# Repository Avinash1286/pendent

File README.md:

# AURA / pendent

**Capture the context of your life.**

[Explore the A03 showcase](https://pendent-eight.vercel.app) · [Watch the A03 film](https://pendent-eight.vercel.app/film/aura-launch.mp4) · [Download the A03 release](https://github.com/Avinash1286/pendent/releases/tag/a03-context-dev) · [Run the notes portal](portal/README.md)

An open product-development project for a compact necklace AI note-taking device. Electronics, printable industrial design, chip firmware, local transcription, a Next.js / Convex notes portal, an interactive Three.js showcase and a Hyperframes launch film live together here.

## A04 circular redesign — in progress

A04 is a fresh circular design created through **KiCad MCP**, with a physical microphone disconnect, separate update-storage hardware and a source-preserving audio protocol. The current M2 mechanism is **43 mm across and 12.2 mm deep**, accommodating the actual 1.6 mm draft PCB and a 4.3 mm pack allowance. An 11.2 mm variant requires an unselected thinner pack. The earlier 40 × 10 mm goal remains an aspiration, not the dimensions of these files. **A04 is not ready to fabricate, print as a complete device, wear or sell.**

[Full objective and evidence gates](docs/a04/requirements.md) · [New KiCad project](hardware/a04/aura-a04.kicad_pro) · [Mechanical contract](docs/a04/industrial-design.md) · [Software contract and recovery tests](docs/a04/software-contract.md) · [Omi source review](docs/research/omi-review.md)

The current checkpoint includes a **72-reference schematic candidate**, monitored microphone driver, bounded audio FIFO, recorder, shared C/Python Opus archive, recoverable NAND journal and SPI command core. The [storage owner and release outbox](firmware/a04/STORAGE.md) now reserve capture identities and release explicitly authorized recordings through a durable grant, with real C/Python audio round trips on modeled NAND. The nRF52840 DK build records linked memory and symbols in [the current wired-bench ELF resource report](firmware/a04/bench/verification/arm-resources.json). Host checks cover driver faults, privacy/stop ordering, capture boundaries, interrupted writes and preserved audio during storage reuse. The companion passes 131 tests; the earlier portal checkpoint retains 24. The schematic still has one ERC error, nine warnings and three net-name mismatches; the board is not placed or routed. [Native capture evidence](docs/a04/native-capture-verification.json) · [Firmware and audio evidence](firmware/a04/README.md) · [Route to your first physical wearable](docs/research/aura-first-wearable.md).

The working local software path now takes a **real C-generated audio archive through local Whisper transcription into Next.js/Convex**. It preserves the original capture, exact audio duration, bookmarks and transcript provenance. Interrupted captures remain explicit, and token rotation does not duplicate an existing source. These checks use synthetic speech; microphone, Bluetooth and worn-device behavior still need physical validation. [Try the archive importer](companion/README.md#a04-archive-import--040) · [Read the verification](companion/VERIFICATION.md) · [Portal provenance and recovery](docs/a04/portal-provenance.md).

The new [first spoken-note bench](firmware/a04/bench/README.md) provides a separate nRF52840 DK application, reviewed microphone/NAND wiring and a UART capture/export tool. It connects the actual drivers and storage code, with explicit recording permission and verified local publication. The image cross-builds; 31 host-client tests and five C orchestration groups cover its software behavior. **No physical audio has been recorded or board flashed.** This prepares the hardware experiment needed before the custom PCB and wearable can be qualified.

The [native Android companion](mobile/android/README.md) provides a local recording library: select an A04 archive, validate its original bytes and Opus audio, listen back, write context, and explicitly copy/share that context with an AI chat. The new [durable download store](mobile/android/DOWNLOADS.md) commits exact source records and resume metadata together, replays saved prefixes after reopening, and passes completed downloads through the library's actual decoder and publication checks. The current [development APK](https://github.com/Avinash1286/pendent/releases/tag/a04-android-recovery-dev) passed **29 Android emulator cases / 428 assertions**, with zero lint findings. The shared complete/incremental validator and transfer codecs pass **30 JVM groups / 82,213 checks**, including six incremental groups / 49,471 checks and 19 complete C-generated archives. The real Android GATT path also passed **four virtual-link cases / 33 assertions at each of MTU 23 and 517**, including a second connection without duplicate library entries. The peripheral is a Python fixture, not Zephyr firmware or physical radio. Original recordings and physical-OPEN provenance remain preserved. The Activity still exposes file import; Bluetooth download is not yet a user-facing feature. [Verification](mobile/android/VERIFICATION.md).

A [bounded journal cursor](firmware/a04/JOURNAL-CURSOR.md) prepares pendant-to-phone recovery: exact-record resume, at most one NAND read per step, source checks before streaming and again before completion, and cancellation that preserves the original recording. It is exercised through the wired DK export path. A portable [transfer command owner](docs/a04/transfer-wire-v1.md) adds ordered retries, owned capture selection and protection against stale response callbacks; 12 C test groups pass. Android now has the durable source store, library handoff and [foreground recovery owner with a native GATT client](mobile/android/RECOVERY.md). The device radio DK adapter is now implemented separately; owner enrollment, matching Android proof integration and consumer UI remain, followed by physical recovery and OS background qualification. [Transport integration plan](docs/a04/mobile-transport.md).

The new [authenticated Bluetooth DK application](firmware/a04/radio/README.md) integrates the actual transfer engine with the recording/storage owner. It adds a physically bounded pairing window, authenticated LE Secure Connections and fresh owner proof before archive access. Eighteen GATT/transfer groups, twelve C authentication groups and nine pairing-policy groups pass with their documented modeled boundaries. The ARM image uses 243,652 bytes RAM, leaving 18,492 bytes unallocated; runtime headroom is unmeasured. [Download the DK development build](https://github.com/Avinash1286/pendent/releases/tag/a04-radio-dk-dev). Consumer enrollment, the matching Android proof exchange and physical radio/capture trials remain; the older Android/Bumble tests do not execute this firmware.

The **M2 S1 mechanism** keeps the removable bezel and supported PCB, replacing inadequate resin bending links with a separate steel shoe/support and insulating contact pad. Each depth variant contains **12 polymer part models, three hardware form models and two unpowered gauges**. The metal/film forms are not functional resin-print instructions. Mesh and sampled motion checks cover the revised assembly; analytical force screening supports further unpowered joint testing. Materials, tolerances, switch endpoints, all 72 native PCB features, the battery and real assembly remain unqualified. [Blender source, parts and checks](enclosure/a04/mechanism-m2/README.md) · [Steel development drawings and 1:1 DXF profiles](enclosure/a04/mechanism-m2-manufacturing/README.md) · [Earlier process coupon kit](enclosure/a04/coupon/README.md).

<details>
<summary>Inspect the A04 M2 experimental parts</summary>

The exploded offsets show individual parts; separate motion reports check sampled assembly paths. Read the [remaining assembly and release gates](enclosure/a04/mechanism-m2/README.md#assembly-and-release-gates) before using these files. The [M1 experiment and its failures](enclosure/a04/mechanism/README.md) and [original 40 mm appearance study](enclosure/a04/study/aura-a04-study.png) remain available as earlier work.

</details>

The website, film, PCB and eight-part print kit linked below belong to the earlier **A03 development release**. They are retained for reproducibility and are not A04 deliverables.

## A03 development release

## Launch film

**[▶ Watch the 44-second film](https://pendent-eight.vercel.app/film/aura-launch.mp4)** · [Download the 1080p MP4](https://github.com/Avinash1286/pendent/releases/download/a03-context-dev/aura-launch.mp4) · [Hyperframes source](film/aura-launch/README.md)

See the pendant from the outside in, including its interior and assembly animation. Click the poster to play.

## 3D-printable parts

Rendered from the actual STL files; individual views are not to scale. The kit includes six device parts and two fit/alignment tools. STL units are millimetres; print orientation and material guidance are in the assembly guide.

[Download all eight STL files](enclosure/aura-a03-print-kit.zip) · [Print and assembly guide](enclosure/PRINTING.md) · [Editable Blender scene](enclosure/aura-product.blend)

## PCB

The **24 × 42 × 0.8 mm, four-layer board**, shown directly from its native KiCad copper layers with illustrative colours. These are prototype files; the 78 courtyard findings still require assembly review.

[Editable KiCad project](hardware/native/aura-a03.kicad_pro) · [Prototype fabrication ZIP](hardware/output/aura-a03-prototype-fabrication.zip) · [Schematic and review files](hardware/native/review/)

## Project status

**A03 context and assembly edition.** [Prototype fabrication files](hardware/native/README.md) are exported from the paired KiCad project: zero unconnected items, schematic mismatches, ERC findings or bare-board DRC errors. **78 unsuppressed courtyard overlaps remain for assembly review.** The case has printable meshes with geometric audits; real fit, battery, acoustic and RF tests remain. Firmware is compiled for the nRF52840 but has not run on an assembled AURA. The notes portal uses real local Convex; cloud setup awaits account terms acceptance. This is not a manufactured or certified device, and no orders or payments are accepted. See the [current release guide](docs/release-a03-context.md) for downloads and verification.

## Project map

New: [Omi codebase review and AURA first-wear plan](docs/research/omi-review.md), with a source-based comparison, all 78 assembly collisions classified, and companion recovery improvements. This review identifies a real component-tolerance conflict that requires an A04 placement revision; it does not qualify A03 for assembled-unit ordering.

| Directory | Contents |
| --- | --- |
| `hardware/` | tscircuit source, routed native KiCad board, readable schematic, BOM and validation evidence |
| `enclosure/` | Blender source, editable generator, printable enclosure meshes, GLB and product renders |
| `firmware/` | Zephyr nRF52840 firmware, reproducible tool setup, flashable build artifacts and native tests |
| `companion/` | Bluetooth sync, CRC verification, local Whisper transcription and optional portal upload |
| `mobile/android/` | Native Kotlin local import, durable download storage and replay, verified playback, private context and explicit sharing; A04 wireless integration pending |
| `portal/` | Next.js / Convex private notes, profiles, Context Pack and read-only MCP endpoint |
| `website/` | Interactive React / Three.js product presentation, deployed directly to Vercel |
| `film/` | Hyperframes composition, original soundtrack and rendered launch video |
| `docs/` | Hardware and product engineering notes |

## Design direction

- 48 × 28 × 10 mm capsule body, 54 mm tall including the bail; 24 × 42 mm PCB.
- A glossy black recording paddle in a satin polymer surround, a bookmark gesture, visible microphone-power indication and a physical privacy slider.
- A physical microphone power disconnect, offline local audio storage and Bluetooth transfer to the companion.
- Dual digital microphones, a protected rechargeable-cell candidate and rear contacts for a magnetic charging dock; the complete dock remains to be designed and qualified.
- Local computer transcription and optional notes upload are implemented. The A04 Android source-import and durable download-storage foundation is available; device-to-phone wireless integration remains future work.
- 16 kHz mono PCM storage has an ideal capacity of about 66 minutes before bad blocks and metadata; battery runtime is unmeasured.

## Start exploring

- [Product and interaction specification](docs/product-design.md)
- [Hardware source and validation](hardware/README.md)
- [Print and assembly guide](enclosure/PRINTING.md) · [eight-part print kit](enclosure/aura-a03-print-kit.zip) · [editable Blender scene](enclosure/aura-product.blend)
- [Firmware build / flash / bring-up](firmware/README.md)
- [Install the local companion](companion/README.md)
- [Run AURA Notes and connect any AI](portal/README.md)
- [Launch film and reproducible Hyperframes source](film/aura-launch/README.md)

The portable **Context Pack** combines your selected notes, source excerpts, personal background and current goals into reviewed Markdown. Copy or attach it in ChatGPT, Claude, Gemini, Grok, or another chat. Compatible MCP clients can instead read explicitly approved live context through a revocable bearer token. Provider buttons do not send data automatically.

## Publication

Sources and generated deliverables are shared here. Website deployment uses Vercel directly; this project does not use GitHub Actions. Dependencies, signing keys, tokens, private local recordings and database files are intentionally excluded. Each workstream documents reproducible setup and the checks actually completed.

## Upstream tools

[tscircuit documentation](https://docs.tscircuit.com/) · [Blender](https://www.blender.org/) · [Three.js](https://threejs.org/docs/) · [Hyperframes](https://github.com/heygen-com/hyperframes) · [Vercel](https://vercel.com/docs)

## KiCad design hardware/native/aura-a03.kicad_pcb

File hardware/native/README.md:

# AURA A03 native prototype project

Open **`aura-a03.kicad_pro` in KiCad 10**. This directory is the paired editable PCB and schematic used for the manufacturing exports. The working routing record remains in `../output/aura-a03-native-routing.kicad_pcb`; the original native schematic reconstruction remains in `../output/aura-a03-electrical.kicad_sch`.

The paired project preserves the verified copper and pads, links every footprint to its actual schematic sheet/symbol UUID, and uses project-relative `AURA_PCB` snapshots. Schematic footprint fields match those snapshots. The 37 intentional NC pads receive their schematic singleton net names while remaining physically isolated; internal numeric net codes may change. `project-linkage.json` records the source and packaged board hashes, unchanged routed geometry and unchanged assignments of all 208 intended connected pins. The source paths follow [KiCad's native netlist identity convention](https://docs.kicad.org/doxygen/common_2netlist__reader_2kicad__netlist__reader_8cpp_source.html).

After editing this paired project, regenerate its exports directly. Rebuilding the tscircuit placement does **not** reproduce the completed native routing and must not overwrite it. Review proposed changes in KiCad's Update PCB from Schematic dialog before applying them; preserve the paired UUIDs and exact snapshot land patterns.

## Manufacturing status

These are connected **prototype fabrication and assembly-review files**. Read `review/manufacturing-checks.json` and `review/drc.json` before submitting them. Native ERC, schematic parity, board connectivity and bare-board DRC each have **zero findings**. The complete DRC report retains **78 `courtyards_overlap` errors** for assembly review. This is not an assembly-approved or qualified consumer-device release.

| Directory / file | Purpose |
| --- | --- |
| `fabrication/gerbers/` | Four copper layers, front/back mask and silkscreen, routed outline and Gerber job metadata |
| `fabrication/drills/` | Separate metric plated/nonplated Excellon files, drill maps and tool report |
| `fabrication/aura-a03.ipc` | IPC-D-356 electrical test netlist |
| `assembly/stencil/` | Separate front/back solder-paste Gerbers; stencil/process review required |
| `assembly/bom.csv` | 57 component candidates with MPNs; the four custom copper-contact features are excluded |
| `assembly/component-centres.csv` | Component body/reference positions and source rotations, corrected for the converter origin offsets |
| `assembly/native-footprint-origins.csv` | Raw KiCad origins for audit; includes custom contacts and must not be substituted blindly for component centres |
| `review/board-layers.pdf` / `review/schematic.pdf` | Readable board layers and six schematic sheets |
| `review/erc.json` / `review/drc.json` | Native, unsuppressed check output |
| `review/native-smd-pad-spacing-audit.json` | 25,158 different-net SMD pad pairs checked against 0.15 mm; zero violations |
| `review/native-via-aperture-audit.json` | 177 vias and 88,500 comparisons against actual SMD copper/paste; zero intersections |
| `review/manufacturing-checks.json` | Final export scope, via inventory and file hashes |

All fabrication Gerbers, Excellon drills and component-centre coordinates use the board centre as origin, with positive Y toward the necklace bail. Do not mirror the bottom drill file or apply an additional origin offset. Confirm component zero-angle conventions, underside contact soldering, stencil apertures, panel rails and dense-placement acceptability with the selected assembler.

## Board specification

- Outline: 24 × 42 mm, R10 corners, nominal 0.8 mm FR-4, four copper layers.
- Stack: **JLC04081H-3313** — 35 µm outer copper / 99.4 µm 3313 prepreg / 15.2 µm inner copper / 500 µm core / 15.2 µm inner copper / 99.4 µm 3313 prepreg / 35 µm outer copper. Material sum 0.7992 mm, nominal finished-board order 0.8 mm. No controlled-impedance claim is made.
- Finish: ENIG; green solder mask; white legend. Use a nonconductive enclosure finish over the antenna region.
- Authored minimum trace width 0.10 mm, copper spacing 0.12 mm, hole-to-copper 0.20 mm, hole-to-hole 0.25 mm and copper-to-outline 0.30 mm. Actual different-net SMD pad spacing is separately checked against 0.15 mm.
- Routing vias use **175 plated 0.20 mm drills and two plated 0.15 mm drills**; the microphones also require two 0.50 mm NPTH holes. Order capability for these actual mixed tools, not a blanket 0.20 mm minimum. The smaller tool can incur a supplier surcharge. Vias are tented; no epoxy fill or copper cap is claimed.
- Ground lands use solid connections. Account for thermal mass in stencil/reflow and exposed-pad soldering; do not assume default thermal reliefs.
- The top antenna exclusion applies to copper on all four layers. Chain, enclosure, battery and wearing-position RF tests remain outstanding.

The stack and limits were checked against [JLCPCB's published capabilities](https://jlcpcb.com/capabilities/pcb-capabilities), its [stackup calculator](https://jlcpcb.com/impedance), and [component-spacing guidance](https://jlcpcb.com/help/article/minimum-spacing-for-smd-components). The preserved stackup response is `../sources/jlc-4layer-08mm-stackups.json`. These sources do not constitute factory approval of this particular design. This small board needs supplier-approved panelization and assembly access.

## Prototype bring-up

Use the [firmware bring-up guide](../../firmware/README.md) with current-limited supplies and verified parts. Charging and haptics remain disabled in the distributed firmware pending measurements with the selected battery, NTC and actuator. Battery voltage tolerance, thermal cutoff, audio, RF, physical fit and power consumption remain unqualified. The PCB contacts and alignment jig are supplied; a complete charging-dock production design is not included.

## Reproduce the package

Use KiCad's Python, which includes `pcbnew`, and KiCad 10's CLI. From `hardware/`, after a verified native routing/library freeze:

```powershell
$boardHash = (Get-FileHash output/aura-a03-native-routing.kicad_pcb).Hash
& 'C:/Program Files/KiCad/10.0/bin/python.exe' scripts/pair-native-project.py --expected-sha256 $boardHash
& 'C:/Program Files/KiCad/10.0/bin/python.exe' scripts/audit-native-pad-spacing.py --board native/aura-a03.kicad_pcb
& 'C:/Program Files/KiCad/10.0/bin/python.exe' scripts/audit-native-via-apertures.py --board native/aura-a03.kicad_pcb
& 'C:/Program Files/KiCad/10.0/bin/python.exe' scripts/export-native-package.py
node scripts/package-status.mjs
python scripts/package-native-archive.py
```

The pairing step is for rebuilding the packaged project from the frozen working sources; it overwrites generated files in this directory. For subsequent edits in the paired project, rerun the two clearance audits and the exporter without pairing again. The exporter rejects stale audit hashes and fails on unconnected nets, schematic mismatch, ERC findings or non-assembly DRC errors. The final commands verify file hashes and rebuild the portable prototype archive. These commands do not purchase boards, submit files to a factory, or deploy software.

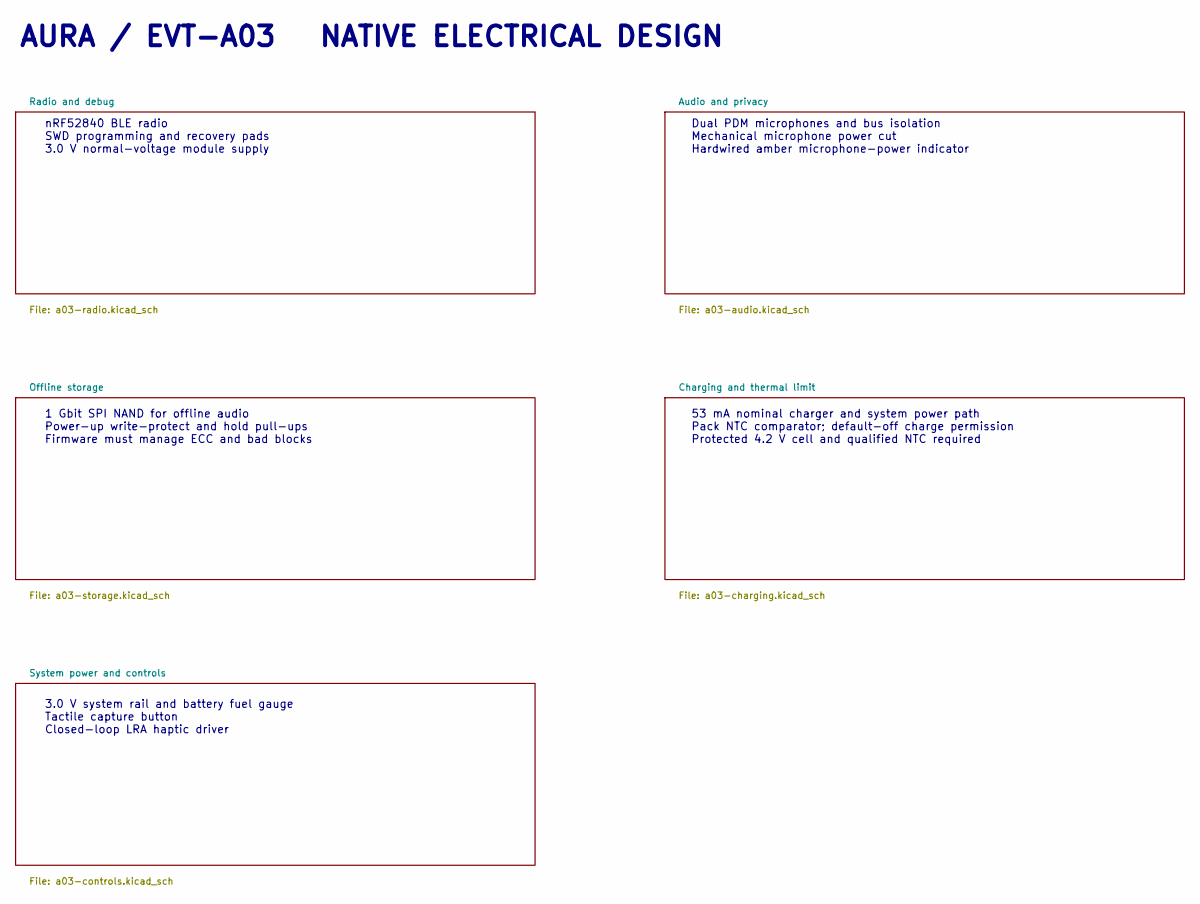
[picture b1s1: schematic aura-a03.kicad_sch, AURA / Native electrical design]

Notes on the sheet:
AURA / EVT-A03 NATIVE ELECTRICAL DESIGN
nRF52840 BLE radio SWD programming and recovery pads 3.0 V normal-voltage module supply
Dual PDM microphones and bus isolation Mechanical microphone power cut Hardwired amber microphone-power indicator
1 Gbit SPI NAND for offline audio Power-up write-protect and hold pull-ups Firmware must manage ECC and bad blocks
53 mA nominal charger and system power path Pack NTC comparator; default-off charge permission Protected 4.2 V cell and qualified NTC required
3.0 V system rail and battery fuel gauge Tactile capture button Closed-loop LRA haptic driver

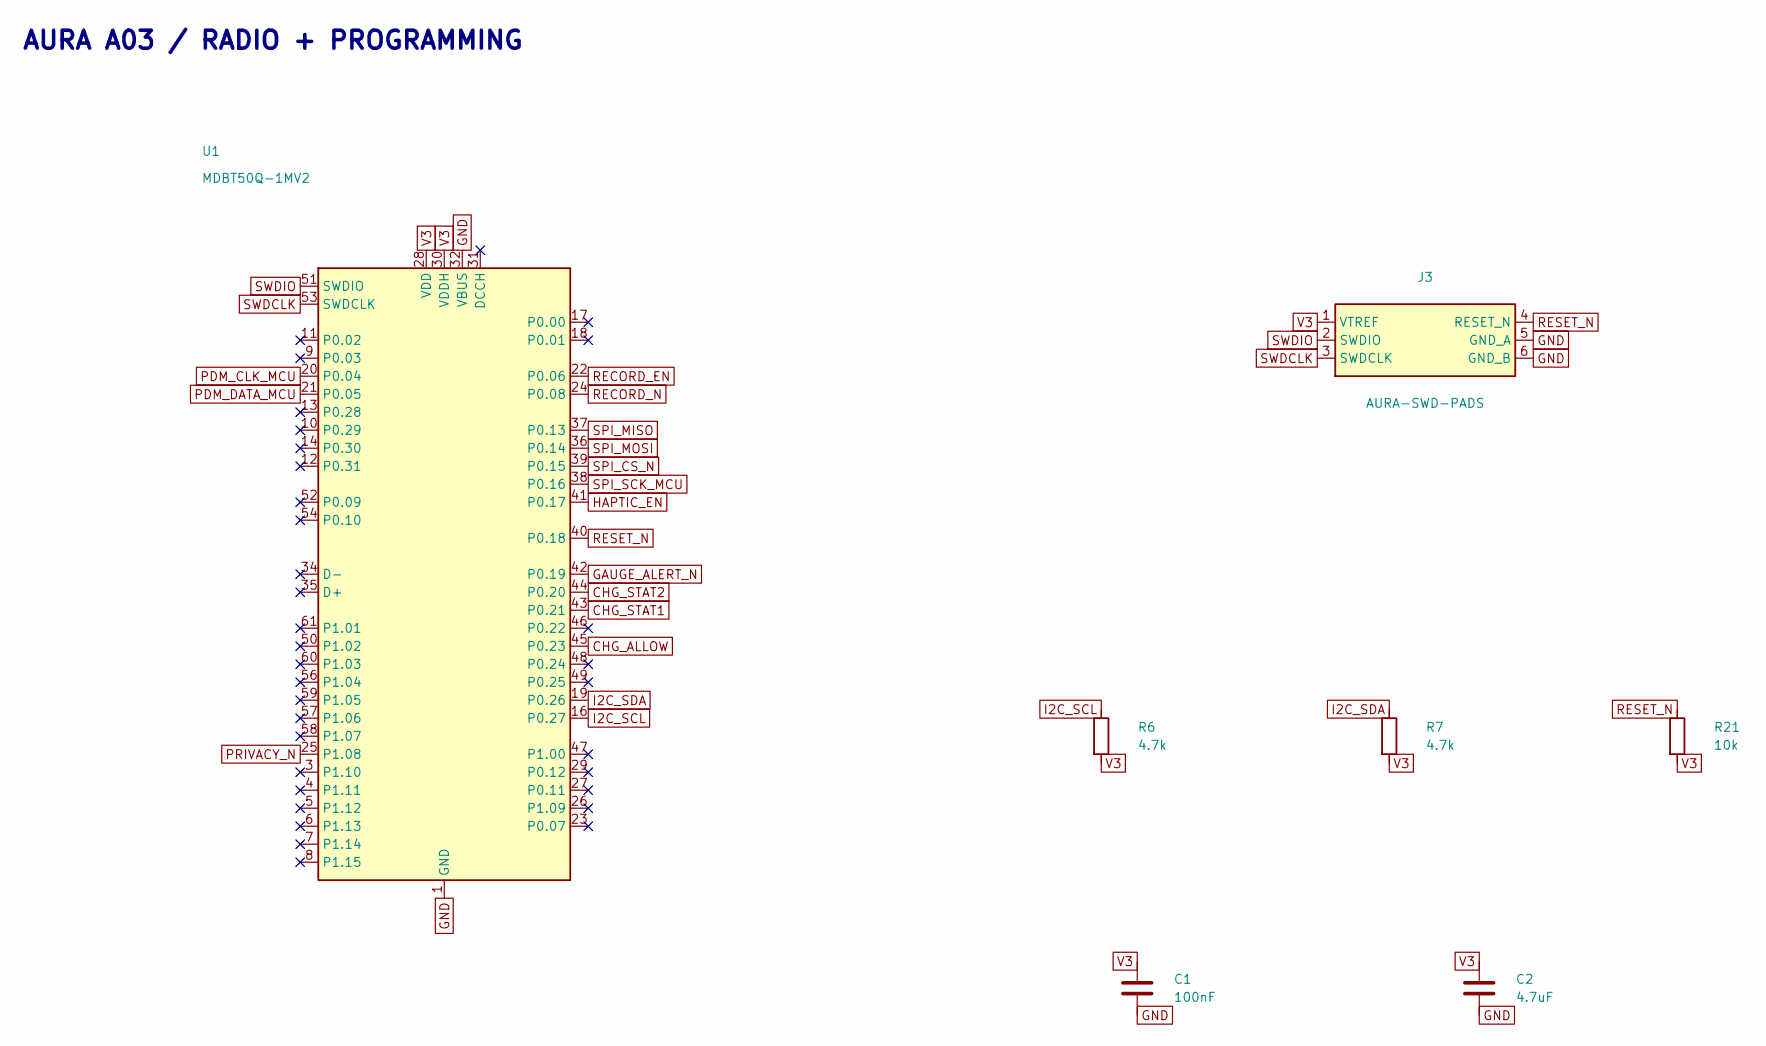
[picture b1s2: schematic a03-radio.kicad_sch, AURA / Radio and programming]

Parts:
C1: 100nF; A03_C1; MPN C0402C104K4RACTU
C2: 4.7uF; A03_C2; MPN C0603C475K8PACTU
J3: AURA-SWD-PADS; A03_J3; MPN AURA-SWD-PADS
R6: 4.7k; A03_R6; MPN RC0402FR-074K7L
R7: 4.7k; A03_R7; MPN RC0402FR-074K7L
R21: 10k; A03_R21; MPN RC0402FR-0710KL
U1: MDBT50Q-1MV2; A03_U1; MPN MDBT50Q-1MV2

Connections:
CHG_ALLOW: U1.45 (P0.23); also elsewhere on the board
CHG_STAT1: U1.43 (P0.21); also elsewhere on the board
CHG_STAT2: U1.44 (P0.20); also elsewhere on the board
GAUGE_ALERT_N: U1.42 (P0.19); also elsewhere on the board
GND: C1.2, C2.2, J3.5 (GND_A), J3.6 (GND_B), U1.1 (GND), U1.2 (GND), U1.15 (GND), U1.32 (VBUS), U1.33 (GND), U1.55 (GND); also elsewhere on the board
HAPTIC_EN: U1.41 (P0.17); also elsewhere on the board
I2C_SCL: R6.1, U1.16 (P0.27); also elsewhere on the board
I2C_SDA: R7.1, U1.19 (P0.26); also elsewhere on the board
PDM_CLK_MCU: U1.20 (P0.04); also elsewhere on the board
PDM_DATA_MCU: U1.21 (P0.05); also elsewhere on the board
PRIVACY_N: U1.25 (P1.08); also elsewhere on the board
RECORD_EN: U1.22 (P0.06); also elsewhere on the board
RECORD_N: U1.24 (P0.08); also elsewhere on the board
RESET_N: J3.4 (RESET_N), R21.1, U1.40 (P0.18)
SPI_CS_N: U1.39 (P0.15); also elsewhere on the board
SPI_MISO: U1.37 (P0.13); also elsewhere on the board
SPI_MOSI: U1.36 (P0.14); also elsewhere on the board
SPI_SCK_MCU: U1.38 (P0.16); also elsewhere on the board
SWDCLK: J3.3 (SWDCLK), U1.53 (SWDCLK)
SWDIO: J3.2 (SWDIO), U1.51 (SWDIO)
V3: C1.1, C2.1, J3.1 (VTREF), R6.2, R7.2, R21.2, U1.28 (VDD), U1.30 (VDDH); also elsewhere on the board

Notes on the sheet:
AURA A03 / RADIO + PROGRAMMING

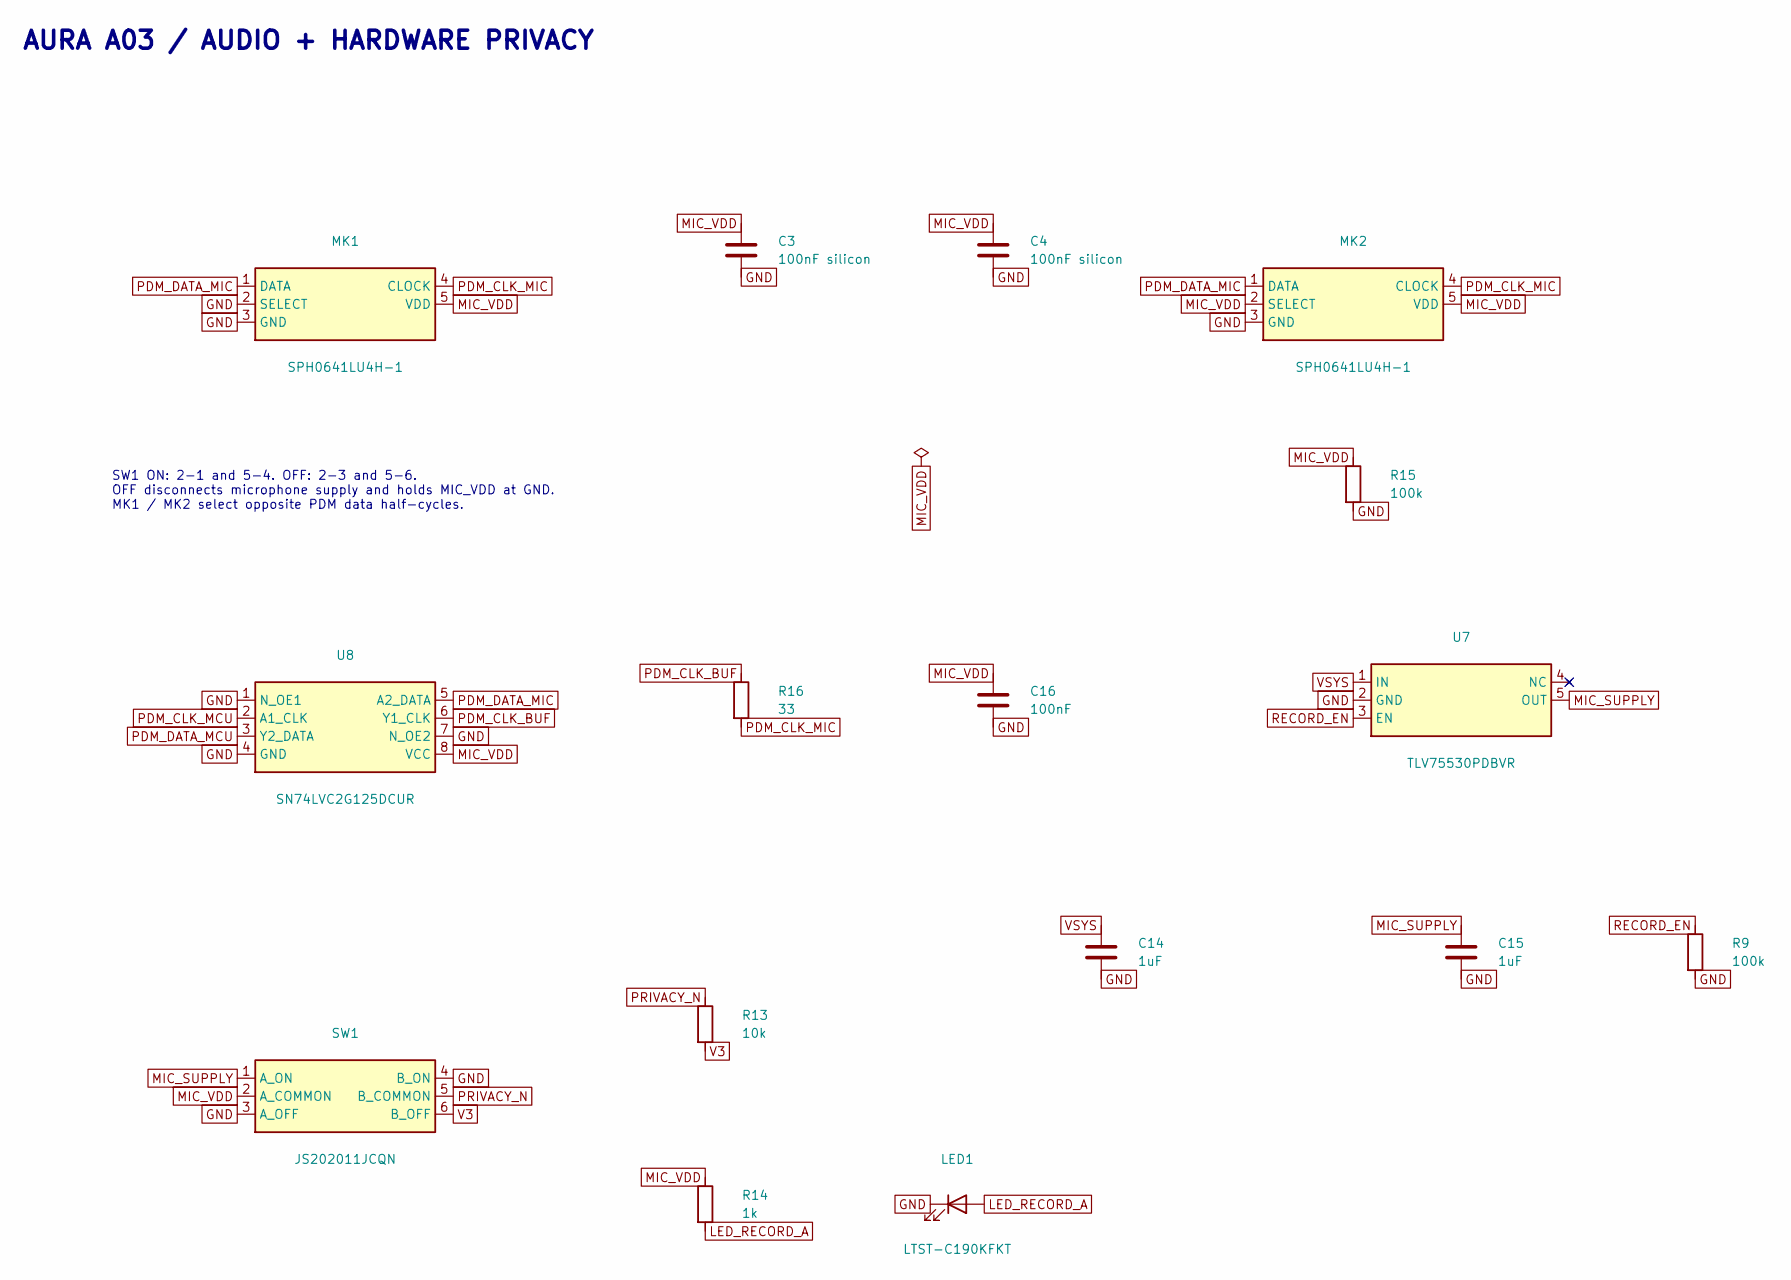
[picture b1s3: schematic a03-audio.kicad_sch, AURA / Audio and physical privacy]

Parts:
C3: 100nF silicon; A03_C3; MPN 939113424610-T3N
C4: 100nF silicon; A03_C4; MPN 939113424610-T3N
C14: 1uF; A03_C14; MPN C0603C105K4RACTU
C15: 1uF; A03_C15; MPN C0603C105K4RACTU
C16: 100nF; A03_C16; MPN C0402C104K4RACTU
LED1: LTST-C190KFKT; A03_LED1; MPN LTST-C190KFKT
MK1: SPH0641LU4H-1; A03_MK1; MPN SPH0641LU4H-1
MK2: SPH0641LU4H-1; A03_MK2; MPN SPH0641LU4H-1
R9: 100k; A03_R9; MPN RC0402FR-07100KL
R13: 10k; A03_R13; MPN RC0402FR-0710KL
R14: 1k; A03_R14; MPN RC0402FR-071KL
R15: 100k; A03_R15; MPN RC0402FR-07100KL
R16: 33; A03_R16; MPN RC0402FR-0733RL
SW1: JS202011JCQN; A03_SW1; MPN JS202011JCQN
U7: TLV75530PDBVR; A03_U7; MPN TLV75530PDBVR
U8: SN74LVC2G125DCUR; A03_U8; MPN SN74LVC2G125DCUR

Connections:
GND: C3.2, C4.2, C14.2, C15.2, C16.2, LED1.1 (K), MK1.2 (SELECT), MK1.3 (GND), MK2.3 (GND), R9.2, R15.2, SW1.3 (A_OFF), SW1.4 (B_ON), U7.2 (GND), U8.1 (N_OE1), U8.4 (GND), U8.7 (N_OE2); also elsewhere on the board
LED_RECORD_A: LED1.2 (A), R14.2
MIC_SUPPLY: C15.1, SW1.1 (A_ON), U7.5 (OUT)
MIC_VDD: C3.1, C4.1, C16.1, MK1.5 (VDD), MK2.2 (SELECT), MK2.5 (VDD), R14.1, R15.1, SW1.2 (A_COMMON), U8.8 (VCC)
PDM_CLK_BUF: R16.1, U8.6 (Y1_CLK)
PDM_CLK_MCU: U8.2 (A1_CLK); also elsewhere on the board
PDM_CLK_MIC: MK1.4 (CLOCK), MK2.4 (CLOCK), R16.2
PDM_DATA_MCU: U8.3 (Y2_DATA); also elsewhere on the board
PDM_DATA_MIC: MK1.1 (DATA), MK2.1 (DATA), U8.5 (A2_DATA)
PRIVACY_N: R13.1, SW1.5 (B_COMMON); also elsewhere on the board
RECORD_EN: R9.1, U7.3 (EN); also elsewhere on the board
V3: R13.2, SW1.6 (B_OFF); also elsewhere on the board
VSYS: C14.1, U7.1 (IN); also elsewhere on the board

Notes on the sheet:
AURA A03 / AUDIO + HARDWARE PRIVACY
SW1 ON: 2-1 and 5-4. OFF: 2-3 and 5-6. OFF disconnects microphone supply and holds MIC_VDD at GND. MK1 / MK2 select opposite PDM data half-cycles.

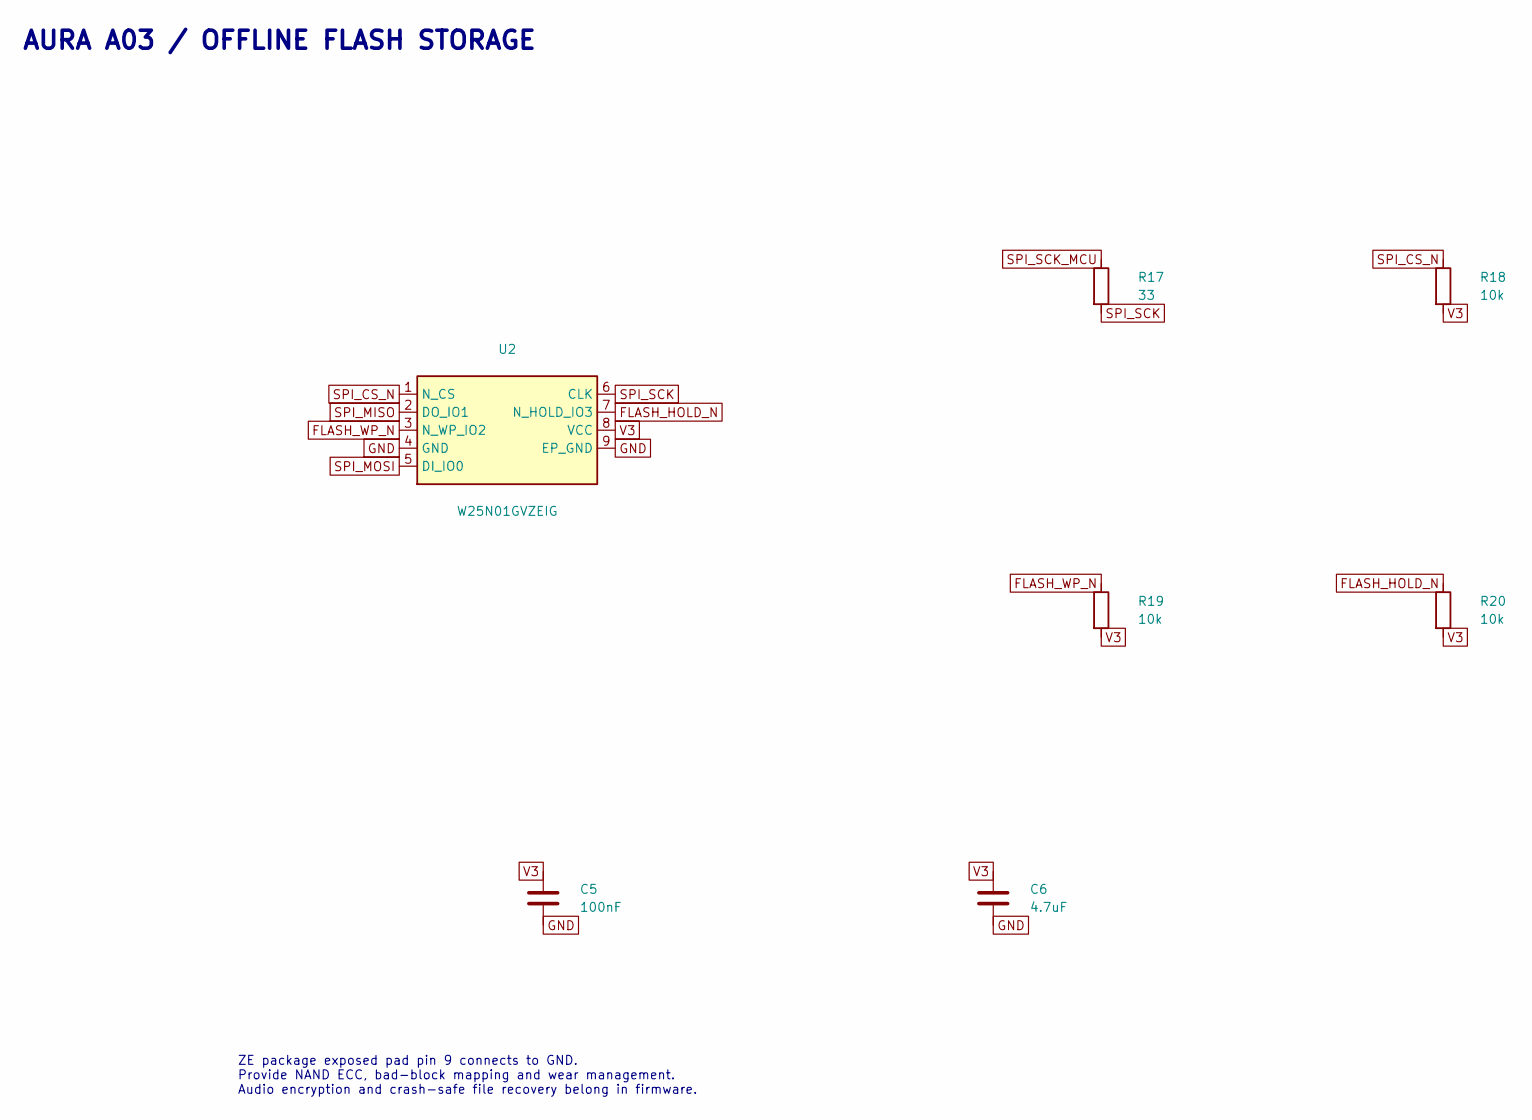
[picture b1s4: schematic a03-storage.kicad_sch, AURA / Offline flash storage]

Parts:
C5: 100nF; A03_C5; MPN C0402C104K4RACTU
C6: 4.7uF; A03_C6; MPN C0603C475K8PACTU
R17: 33; A03_R17; MPN RC0402FR-0733RL
R18: 10k; A03_R18; MPN RC0402FR-0710KL
R19: 10k; A03_R19; MPN RC0402FR-0710KL
R20: 10k; A03_R20; MPN RC0402FR-0710KL
U2: W25N01GVZEIG; A03_U2; MPN W25N01GVZEIG

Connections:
FLASH_HOLD_N: R20.1, U2.7 (N_HOLD_IO3)
FLASH_WP_N: R19.1, U2.3 (N_WP_IO2)
GND: C5.2, C6.2, U2.4 (GND), U2.9 (EP_GND); also elsewhere on the board
SPI_CS_N: R18.1, U2.1 (N_CS); also elsewhere on the board
SPI_MISO: U2.2 (DO_IO1); also elsewhere on the board
SPI_MOSI: U2.5 (DI_IO0); also elsewhere on the board
SPI_SCK: R17.2, U2.6 (CLK)
SPI_SCK_MCU: R17.1; also elsewhere on the board
V3: C5.1, C6.1, R18.2, R19.2, R20.2, U2.8 (VCC); also elsewhere on the board

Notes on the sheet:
AURA A03 / OFFLINE FLASH STORAGE
ZE package exposed pad pin 9 connects to GND. Provide NAND ECC, bad-block mapping and wear management. Audio encryption and crash-safe file recovery belong in firmware.

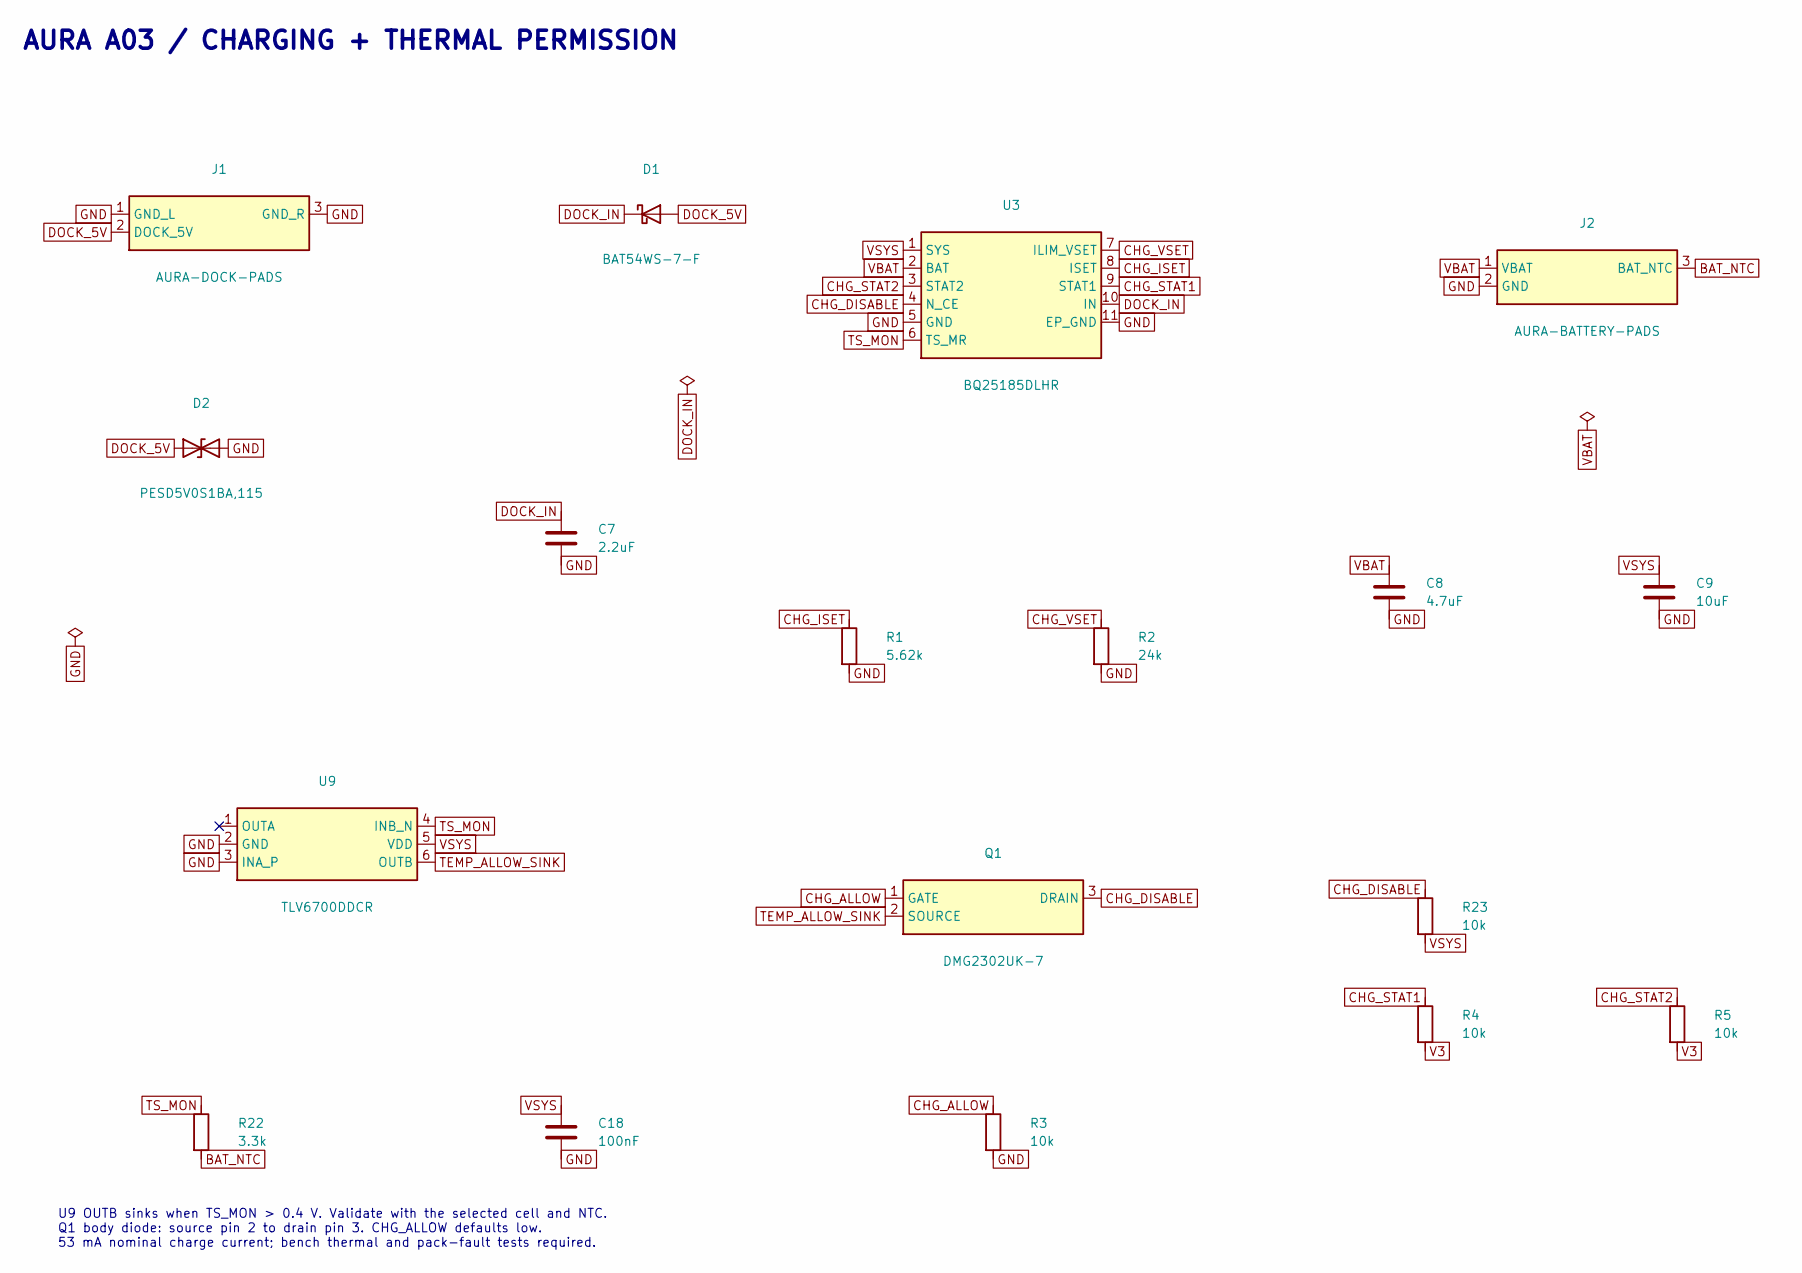
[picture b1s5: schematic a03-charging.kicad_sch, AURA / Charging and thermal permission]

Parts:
C7: 2.2uF; A03_C7; MPN C0603C225K8RACTU
C8: 4.7uF; A03_C8; MPN C0603C475K8PACTU
C9: 10uF; A03_C9; MPN C0805C106K8PACTU
C18: 100nF; A03_C18; MPN C0402C104K4RACTU
D1: BAT54WS-7-F; A03_D1; MPN BAT54WS-7-F
D2: PESD5V0S1BA,115; A03_D2; MPN PESD5V0S1BA,115
J1: AURA-DOCK-PADS; A03_J1; MPN AURA-DOCK-PADS
J2: AURA-BATTERY-PADS; A03_J2; MPN AURA-BATTERY-PADS
Q1: DMG2302UK-7; A03_Q1; MPN DMG2302UK-7
R1: 5.62k; A03_R1; MPN RC0402FR-075K62L
R2: 24k; A03_R2; MPN RC0402FR-0724KL
R3: 10k; A03_R3; MPN RC0402FR-0710KL
R4: 10k; A03_R4; MPN RC0402FR-0710KL
R5: 10k; A03_R5; MPN RC0402FR-0710KL
R22: 3.3k; A03_R22; MPN RC0402FR-073K3L
R23: 10k; A03_R23; MPN RC0402FR-0710KL
U3: BQ25185DLHR; A03_U3; MPN BQ25185DLHR
U9: TLV6700DDCR; A03_U9; MPN TLV6700DDCR

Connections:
BAT_NTC: J2.3 (BAT_NTC), R22.2
CHG_ALLOW: Q1.1 (GATE), R3.1; also elsewhere on the board
CHG_DISABLE: Q1.3 (DRAIN), R23.1, U3.4 (N_CE)
CHG_ISET: R1.1, U3.8 (ISET)
CHG_STAT1: R4.1, U3.9 (STAT1); also elsewhere on the board
CHG_STAT2: R5.1, U3.3 (STAT2); also elsewhere on the board
CHG_VSET: R2.1, U3.7 (ILIM_VSET)
DOCK_5V: D1.2 (A), D2.1 (A1), J1.2 (DOCK_5V)
DOCK_IN: C7.1, D1.1 (K), U3.10 (IN)
GND: C7.2, C8.2, C9.2, C18.2, D2.2 (A2), J1.1 (GND_L), J1.3 (GND_R), J2.2 (GND), R1.2, R2.2, R3.2, U3.5 (GND), U3.11 (EP_GND), U9.2 (GND), U9.3 (INA_P); also elsewhere on the board
TEMP_ALLOW_SINK: Q1.2 (SOURCE), U9.6 (OUTB)
TS_MON: R22.1, U3.6 (TS_MR), U9.4 (INB_N)
V3: R4.2, R5.2; also elsewhere on the board
VBAT: C8.1, J2.1 (VBAT), U3.2 (BAT); also elsewhere on the board
VSYS: C9.1, C18.1, R23.2, U3.1 (SYS), U9.5 (VDD); also elsewhere on the board

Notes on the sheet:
AURA A03 / CHARGING + THERMAL PERMISSION
U9 OUTB sinks when TS_MON > 0.4 V. Validate with the selected cell and NTC. Q1 body diode: source pin 2 to drain pin 3. CHG_ALLOW defaults low. 53 mA nominal charge current; bench thermal and pack-fault tests required.

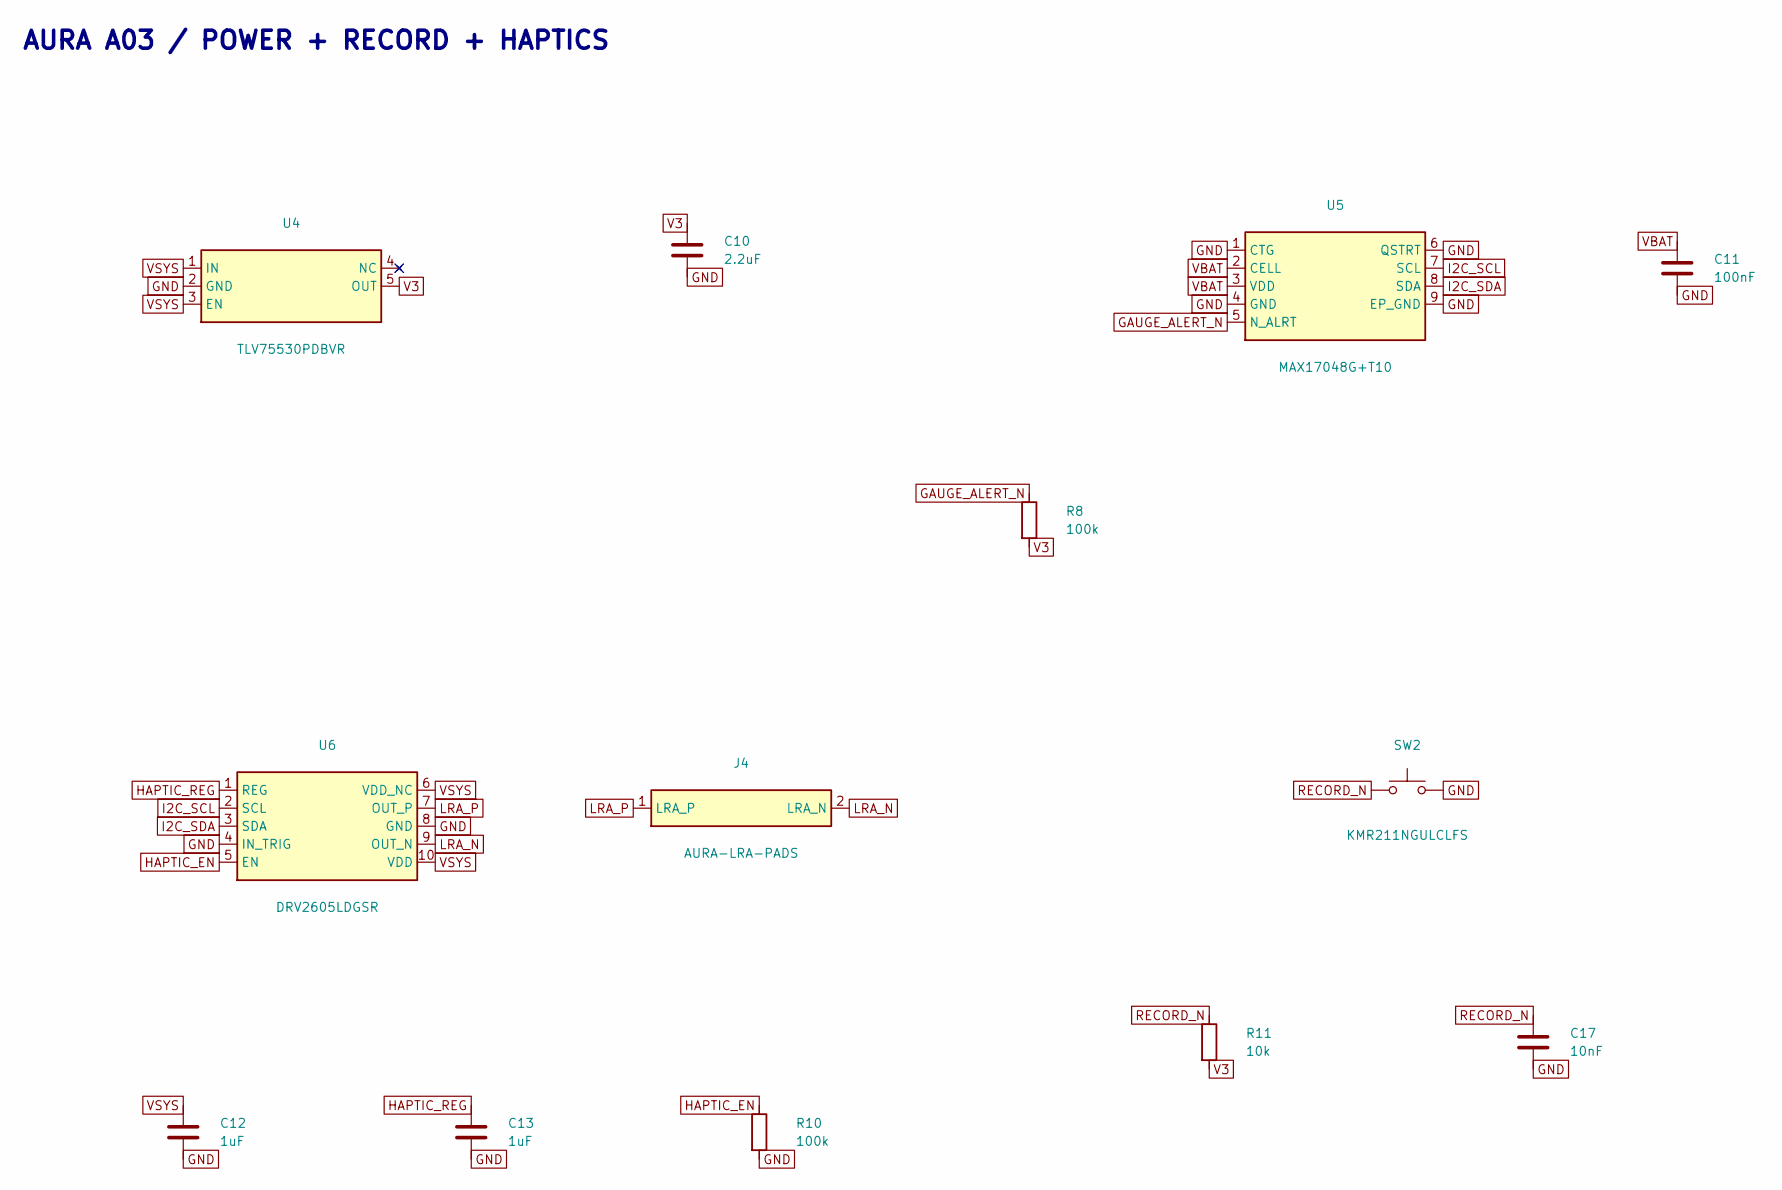
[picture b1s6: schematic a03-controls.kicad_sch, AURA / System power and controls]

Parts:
C10: 2.2uF; A03_C10; MPN C0603C225K8RACTU
C11: 100nF; A03_C11; MPN C0402C104K4RACTU
C12: 1uF; A03_C12; MPN C0603C105K4RACTU
C13: 1uF; A03_C13; MPN C0603C105K4RACTU
C17: 10nF; A03_C17; MPN C0402C103K5RACTU
J4: AURA-LRA-PADS; A03_J4; MPN AURA-LRA-PADS
R8: 100k; A03_R8; MPN RC0402FR-07100KL
R10: 100k; A03_R10; MPN RC0402FR-07100KL
R11: 10k; A03_R11; MPN RC0402FR-0710KL
SW2: KMR211NGULCLFS; A03_SW2; MPN KMR211NGULCLFS
U4: TLV75530PDBVR; A03_U4; MPN TLV75530PDBVR
U5: MAX17048G+T10; A03_U5; MPN MAX17048G+T10
U6: DRV2605LDGSR; A03_U6; MPN DRV2605LDGSR

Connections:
GAUGE_ALERT_N: R8.1, U5.5 (N_ALRT); also elsewhere on the board
GND: C10.2, C11.2, C12.2, C13.2, C17.2, R10.2, SW2.2, U4.2 (GND), U5.1 (CTG), U5.4 (GND), U5.6 (QSTRT), U5.9 (EP_GND), U6.4 (IN_TRIG), U6.8 (GND); also elsewhere on the board
HAPTIC_EN: R10.1, U6.5 (EN); also elsewhere on the board
HAPTIC_REG: C13.1, U6.1 (REG)
I2C_SCL: U5.7 (SCL), U6.2 (SCL); also elsewhere on the board
I2C_SDA: U5.8 (SDA), U6.3 (SDA); also elsewhere on the board
LRA_N: J4.2 (LRA_N), U6.9 (OUT_N)
LRA_P: J4.1 (LRA_P), U6.7 (OUT_P)
RECORD_N: C17.1, R11.1, SW2.1; also elsewhere on the board
V3: C10.1, R8.2, R11.2, U4.5 (OUT); also elsewhere on the board
VBAT: C11.1, U5.2 (CELL), U5.3 (VDD); also elsewhere on the board
VSYS: C12.1, U4.1 (IN), U4.3 (EN), U6.6 (VDD_NC), U6.10 (VDD); also elsewhere on the board

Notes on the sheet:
AURA A03 / POWER + RECORD + HAPTICS
